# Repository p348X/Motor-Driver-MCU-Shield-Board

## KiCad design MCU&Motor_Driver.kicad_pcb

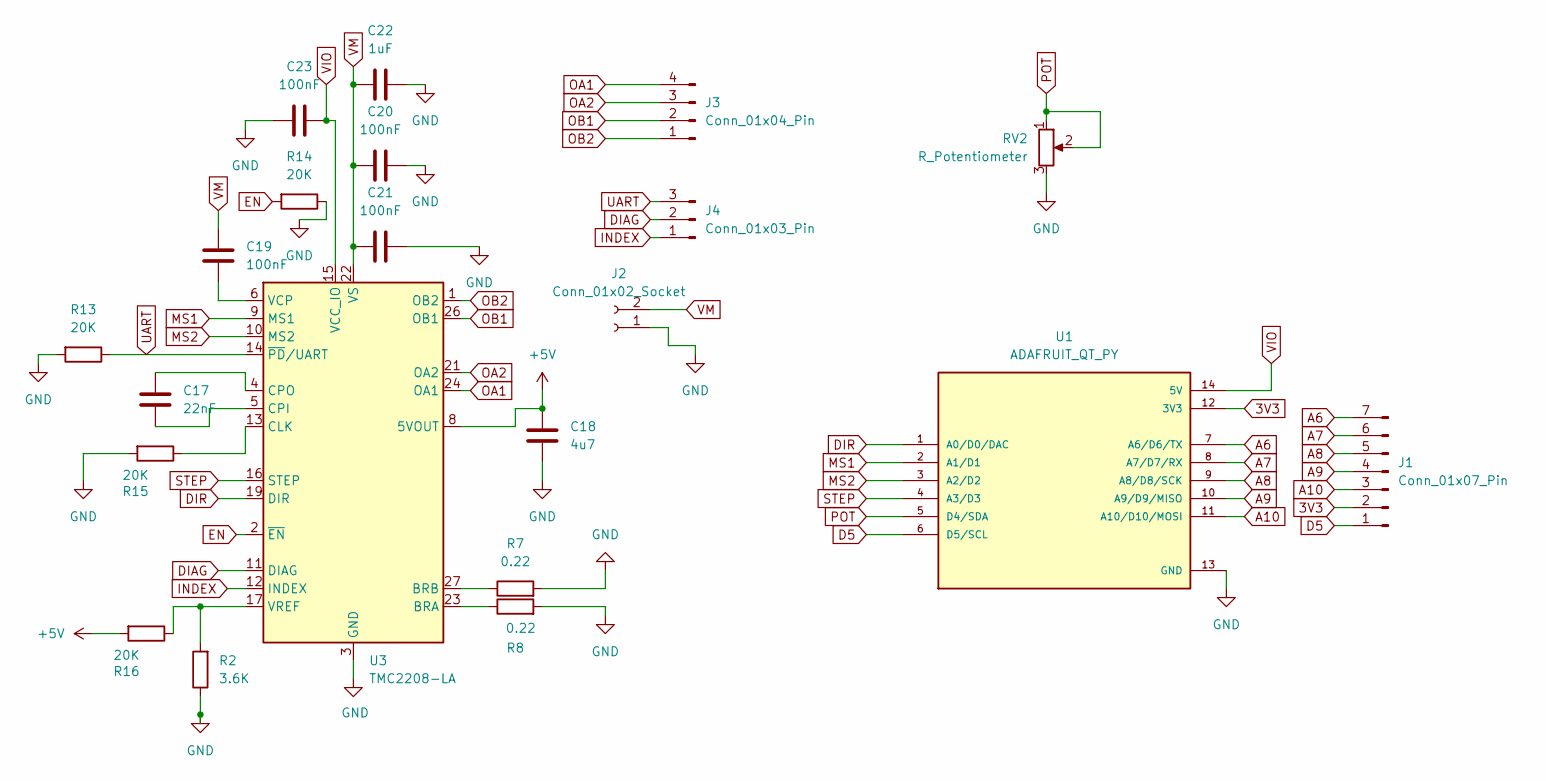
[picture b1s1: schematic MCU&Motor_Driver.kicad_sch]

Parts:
C17: 22nF; C_0805_2012Metric
C18: 4u7; C_0201_0603Metric_Pad0.64x0.40mm_HandSolder
C19, C20, C21, C23: 100nF; C_0402_1005Metric
C22: 1uF; C_0402_1005Metric
J1: Conn_01x07_Pin; PinHeader_1x07_P2.54mm_Vertical
J2: Conn_01x02_Socket; PinHeader_1x02_P2.54mm_Vertical_SMD_Pin1Left
J3: Conn_01x04_Pin; JST_EH_B4B-EH-A_1x04_P2.50mm_Vertical
J4: Conn_01x03_Pin; PinHeader_1x03_P2.54mm_Vertical
R2: 3.6K; R_0402_1005Metric
R7, R8: 0.22; R_0402_1005Metric
R13, R14, R15, R16: 20K; R_0402_1005Metric
RV2: R_Potentiometer; Potentiometer_Bourns_PTV09A-1_Single_Vertical
U1: ADAFRUIT_QT_PY; MODULE_ADAFRUIT_QT_PY; PARTREV 2022-12-12
U3: TMC2208-LA; QFN-28-1EP_5x5mm_P0.5mm_EP3.1x3.1mm

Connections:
3V3: J1.2, U1.12 (3V3)
+5V: C18.1, R16.2, U3.8 (5VOUT)
A6: J1.7, U1.7 (A6/D6/TX)
A7: J1.6, U1.8 (A7/D7/RX)
A8: J1.5, U1.9 (A8/D8/SCK)
A9: J1.4, U1.10 (A9/D9/MISO)
A10: J1.3, U1.11 (A10/D10/MOSI)
D5: J1.1, U1.6 (D5/SCL)
DIAG: J4.2, U3.11 (DIAG)
DIR: U1.1 (A0/D0/DAC), U3.19 (DIR)
EN: R14.2, U3.2 (~EN)
GND: C18.2, C20.2, C21.2, C22.2, C23.1, J2.1, R2.1, R7.2, R8.2, R13.2, R14.1, R15.2, RV2.3, U1.13 (GND), U3.3 (GND), U3.18 (GND), U3.29 (GND)
INDEX: J4.1, U3.12 (INDEX)
MS1: U1.2 (A1/D1), U3.9 (MS1)
MS2: U1.3 (A2/D2), U3.10 (MS2)
unnamed: R8.1, U3.23 (BRA)
unnamed: R7.1, U3.27 (BRB)
unnamed: R15.1, U3.13 (CLK)
unnamed: C17.1, U3.5 (CPI)
unnamed: C17.2, U3.4 (CPO)
unnamed: C19.1, U3.6 (VCP)
unnamed: R2.2, R16.1, U3.17 (VREF)
OA1: J3.4, U3.24 (OA1)
OA2: J3.3, U3.21 (OA2)
OB1: J3.2, U3.26 (OB1)
OB2: J3.1, U3.1 (OB2)
POT: RV2.1, RV2.2, U1.5 (D4/SDA)
STEP: U1.4 (A3/D3), U3.16 (STEP)
UART: J4.3, R13.1, U3.14 (~PD/UART)
VIO: C23.2, U1.14 (5V), U3.15 (VCC_IO)
VM: C19.2, C20.1, C21.1, C22.1, J2.2, U3.22 (VS), U3.28 (VS)

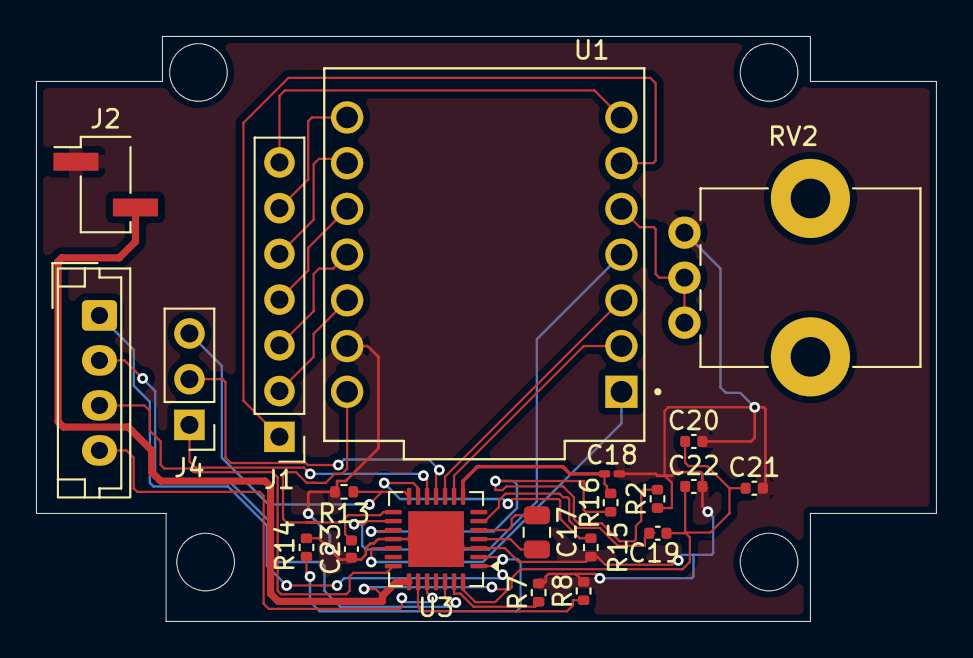
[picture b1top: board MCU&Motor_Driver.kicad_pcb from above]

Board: 4 copper layers, 50.0 x 32.5 mm, 21 parts (0 on the bottom side), 31 nets.
